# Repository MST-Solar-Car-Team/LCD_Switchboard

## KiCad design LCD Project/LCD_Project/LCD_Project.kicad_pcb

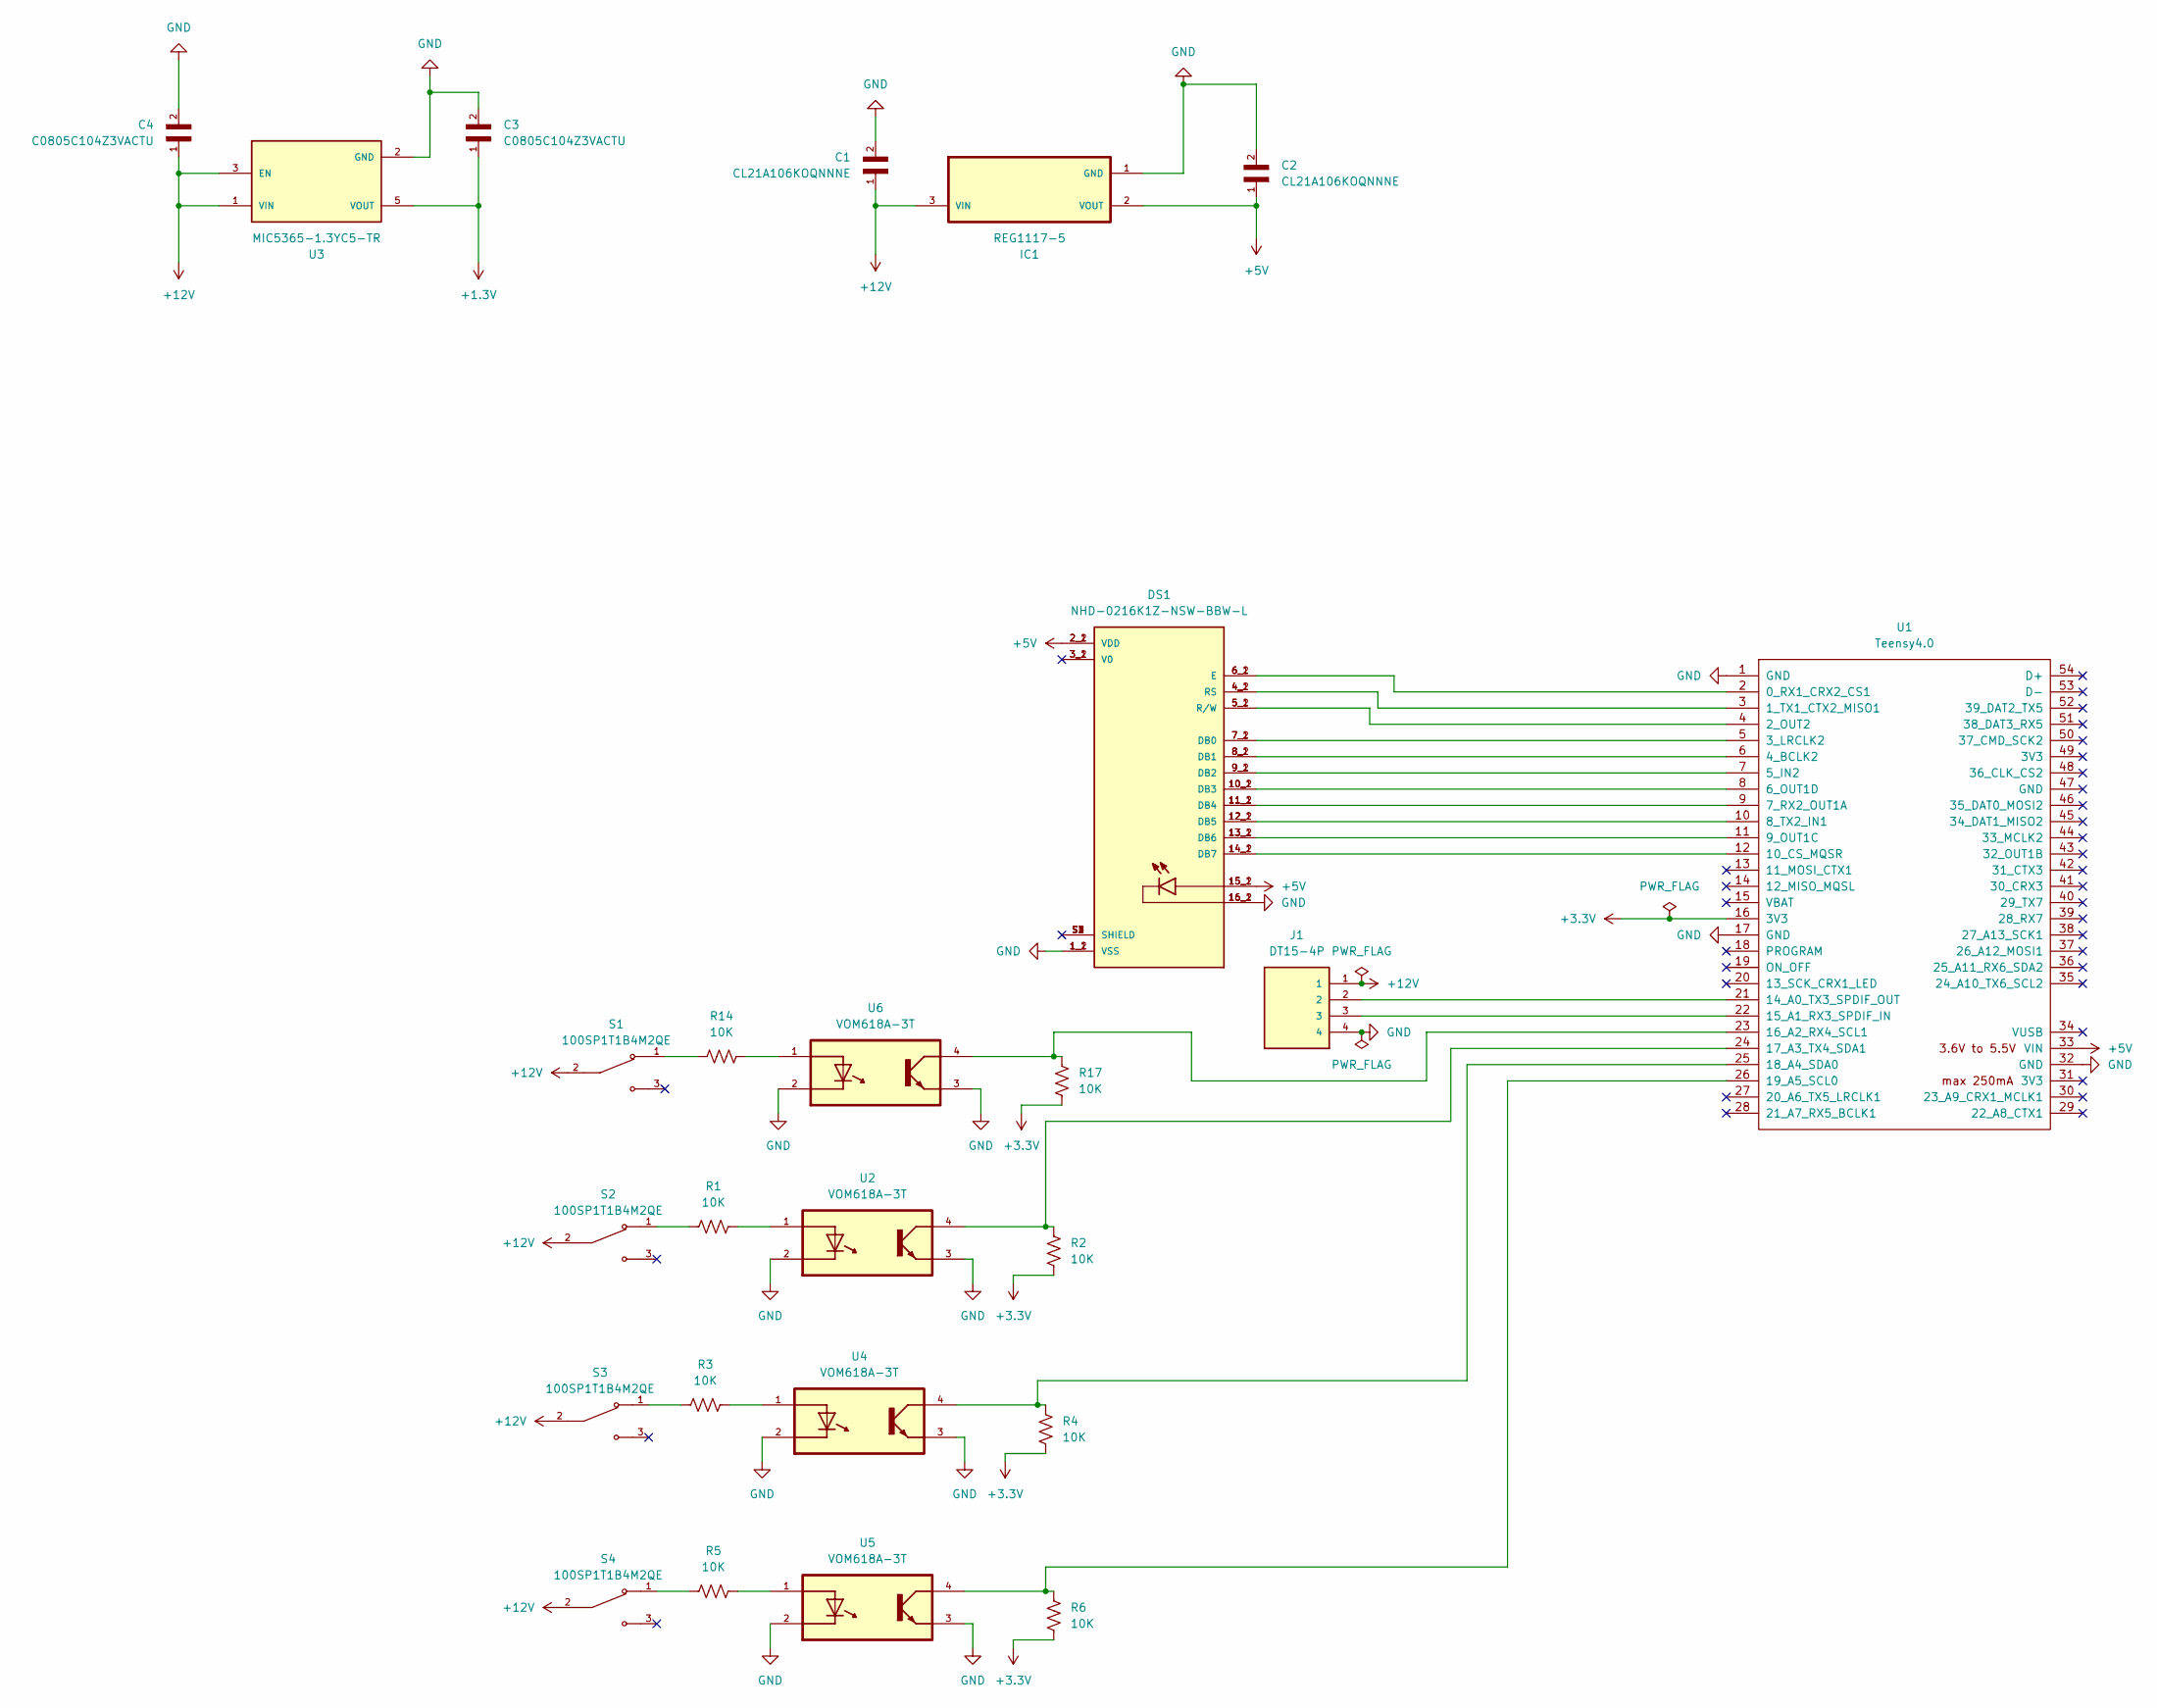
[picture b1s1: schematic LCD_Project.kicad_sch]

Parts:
C1, C2: CL21A106KOQNNNE; CAPC2012X140N
C3, C4: C0805C104Z3VACTU; CAPC2012X88N; DigiKey_Part_Number 399-C0805C104Z3VACTUCT-ND
DS1: NHD-0216K1Z-NSW-BBW-L; NHD_NHD-0216K1Z-NSW-BBW-L; PARTREV 03/28/17
IC1: REG1117-5; SOT230P700X180-4N
J1: DT15-4P; TE_DT15-4P; MPN DT15-4P
R1, R2, R3, R4, R5, R6, R14, R17: 10K; RESC2012X50N
S1, S2, S3, S4: 100SP1T1B4M2QE; SW_100SP1T1B4M2QE; PARTREV E; DigiKey_Part_Number EG2355-ND
U1: Teensy4.0; Teensy40_SMT
U2, U4, U5, U6: VOM618A-3T; SOIC254P695X242-4N
U3: MIC5365-1.3YC5-TR; SOT65P210X110-5N; PARTREV 3.1 - July 16, 2013

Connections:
+3.3V: R2.2, R4.2, R6.2, R17.2, U1.16 (3V3)
+3.7V: DS1.3_1 (V0), DS1.3_2 (V0); also elsewhere on the board
+5V: C2.1, DS1.2_1 (VDD), DS1.2_2 (VDD), DS1.15_1, DS1.15_2, IC1.2 (VOUT), U1.33 (VIN)
+12V: C1.1, C4.1, IC1.3 (VIN), J1.1, S1.2, S2.2, S3.2, S4.2, U3.1 (VIN), U3.3 (EN); also elsewhere on the board
GND: C1.2, C2.2, C3.2, C4.2, DS1.1_1 (VSS), DS1.1_2 (VSS), DS1.16_1, DS1.16_2, IC1.1 (GND), J1.4, U1.1 (GND), U1.17 (GND), U1.32 (GND), U2.2, U2.3, U3.2 (GND), U4.2, U4.3, U5.2, U5.3, U6.2, U6.3; also elsewhere on the board
unnamed: C3.1, U3.5 (VOUT)
unnamed: R1.1, S2.1
unnamed: R1.2, U2.1
unnamed: R3.1, S3.1
unnamed: R3.2, U4.1
unnamed: R5.1, S4.1
unnamed: R5.2, U5.1
unnamed: R14.1, S1.1
unnamed: R14.2, U6.1
unnamed: DS1.6_1 (E), DS1.6_2 (E), U1.2 (0_RX1_CRX2_CS1)
unnamed: DS1.4_1 (RS), DS1.4_2 (RS), U1.3 (1_TX1_CTX2_MISO1)
unnamed: DS1.5_1 (R/W), DS1.5_2 (R/W), U1.4 (2_OUT2)
unnamed: DS1.7_1 (DB0), DS1.7_2 (DB0), U1.5 (3_LRCLK2)
unnamed: DS1.8_1 (DB1), DS1.8_2 (DB1), U1.6 (4_BCLK2)
unnamed: DS1.9_1 (DB2), DS1.9_2 (DB2), U1.7 (5_IN2)
unnamed: DS1.10_1 (DB3), DS1.10_2 (DB3), U1.8 (6_OUT1D)
unnamed: DS1.11_1 (DB4), DS1.11_2 (DB4), U1.9 (7_RX2_OUT1A)
unnamed: DS1.12_1 (DB5), DS1.12_2 (DB5), U1.10 (8_TX2_IN1)
unnamed: DS1.13_1 (DB6), DS1.13_2 (DB6), U1.11 (9_OUT1C)
unnamed: DS1.14_1 (DB7), DS1.14_2 (DB7), U1.12 (10_CS_MQSR)
unnamed: J1.2, U1.21 (14_A0_TX3_SPDIF_OUT)
unnamed: J1.3, U1.22 (15_A1_RX3_SPDIF_IN)
unnamed: R17.1, U1.23 (16_A2_RX4_SCL1), U6.4
unnamed: R2.1, U1.24 (17_A3_TX4_SDA1), U2.4
unnamed: R4.1, U1.25 (18_A4_SDA0), U4.4
unnamed: R6.1, U1.26 (19_A5_SCL0), U5.4

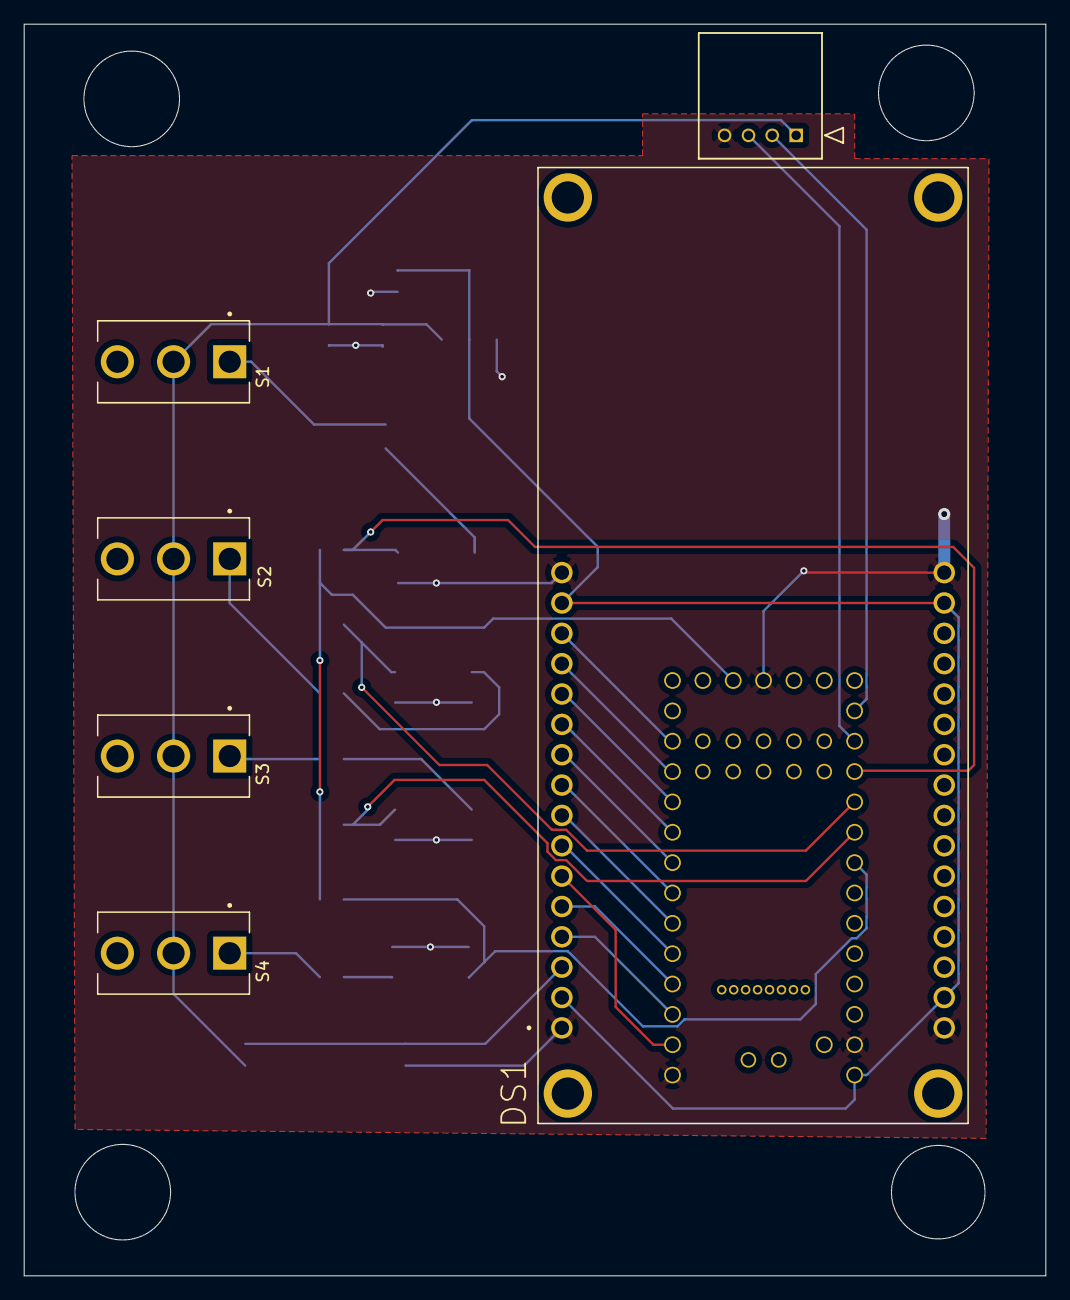
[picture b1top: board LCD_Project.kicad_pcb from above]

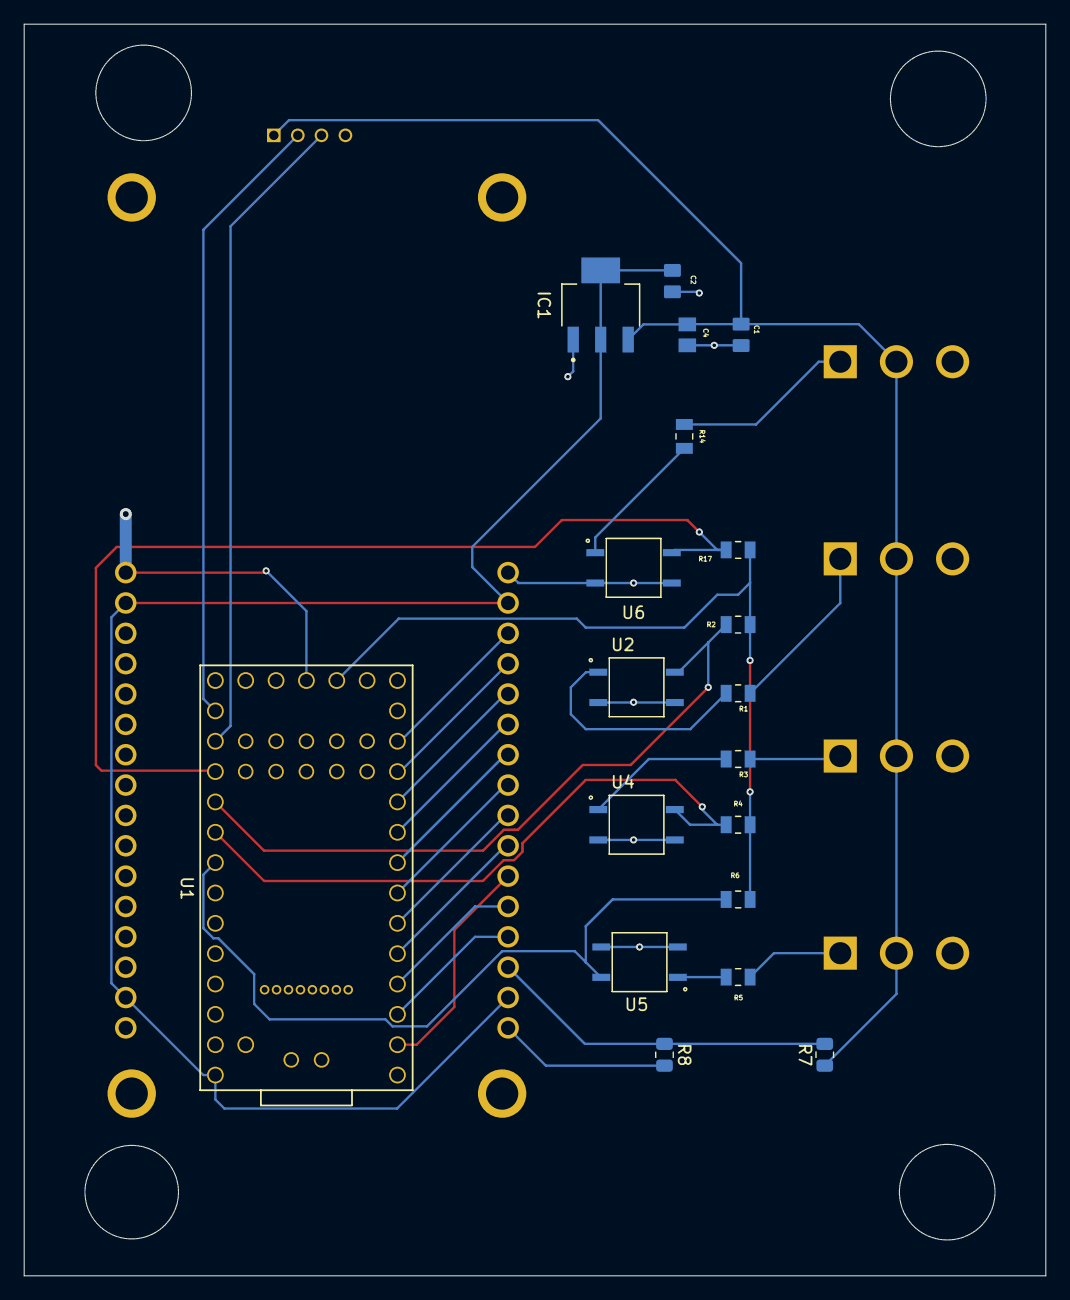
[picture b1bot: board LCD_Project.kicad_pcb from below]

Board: 2 copper layers, 85.5 x 104.8 mm, 25 parts (19 on the bottom side), 30 nets.

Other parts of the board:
R7: R_250; R_0805_2012Metric
R8: R_110; R_0805_2012Metric

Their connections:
+3.7V: R7.2, R8.1; also elsewhere on the board
+12V: R7.1; also elsewhere on the board
GND: R8.2; also elsewhere on the board
